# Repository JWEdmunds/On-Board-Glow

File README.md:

#Micro On-board glow driver project.

Compact 4.8V - 8.4V PWM operated glow driver for RC aircraft

The PCB was designed to be as small as possible without turning it into a fuse. 10x20mm with 0201 components and WLCSP all over the shop.

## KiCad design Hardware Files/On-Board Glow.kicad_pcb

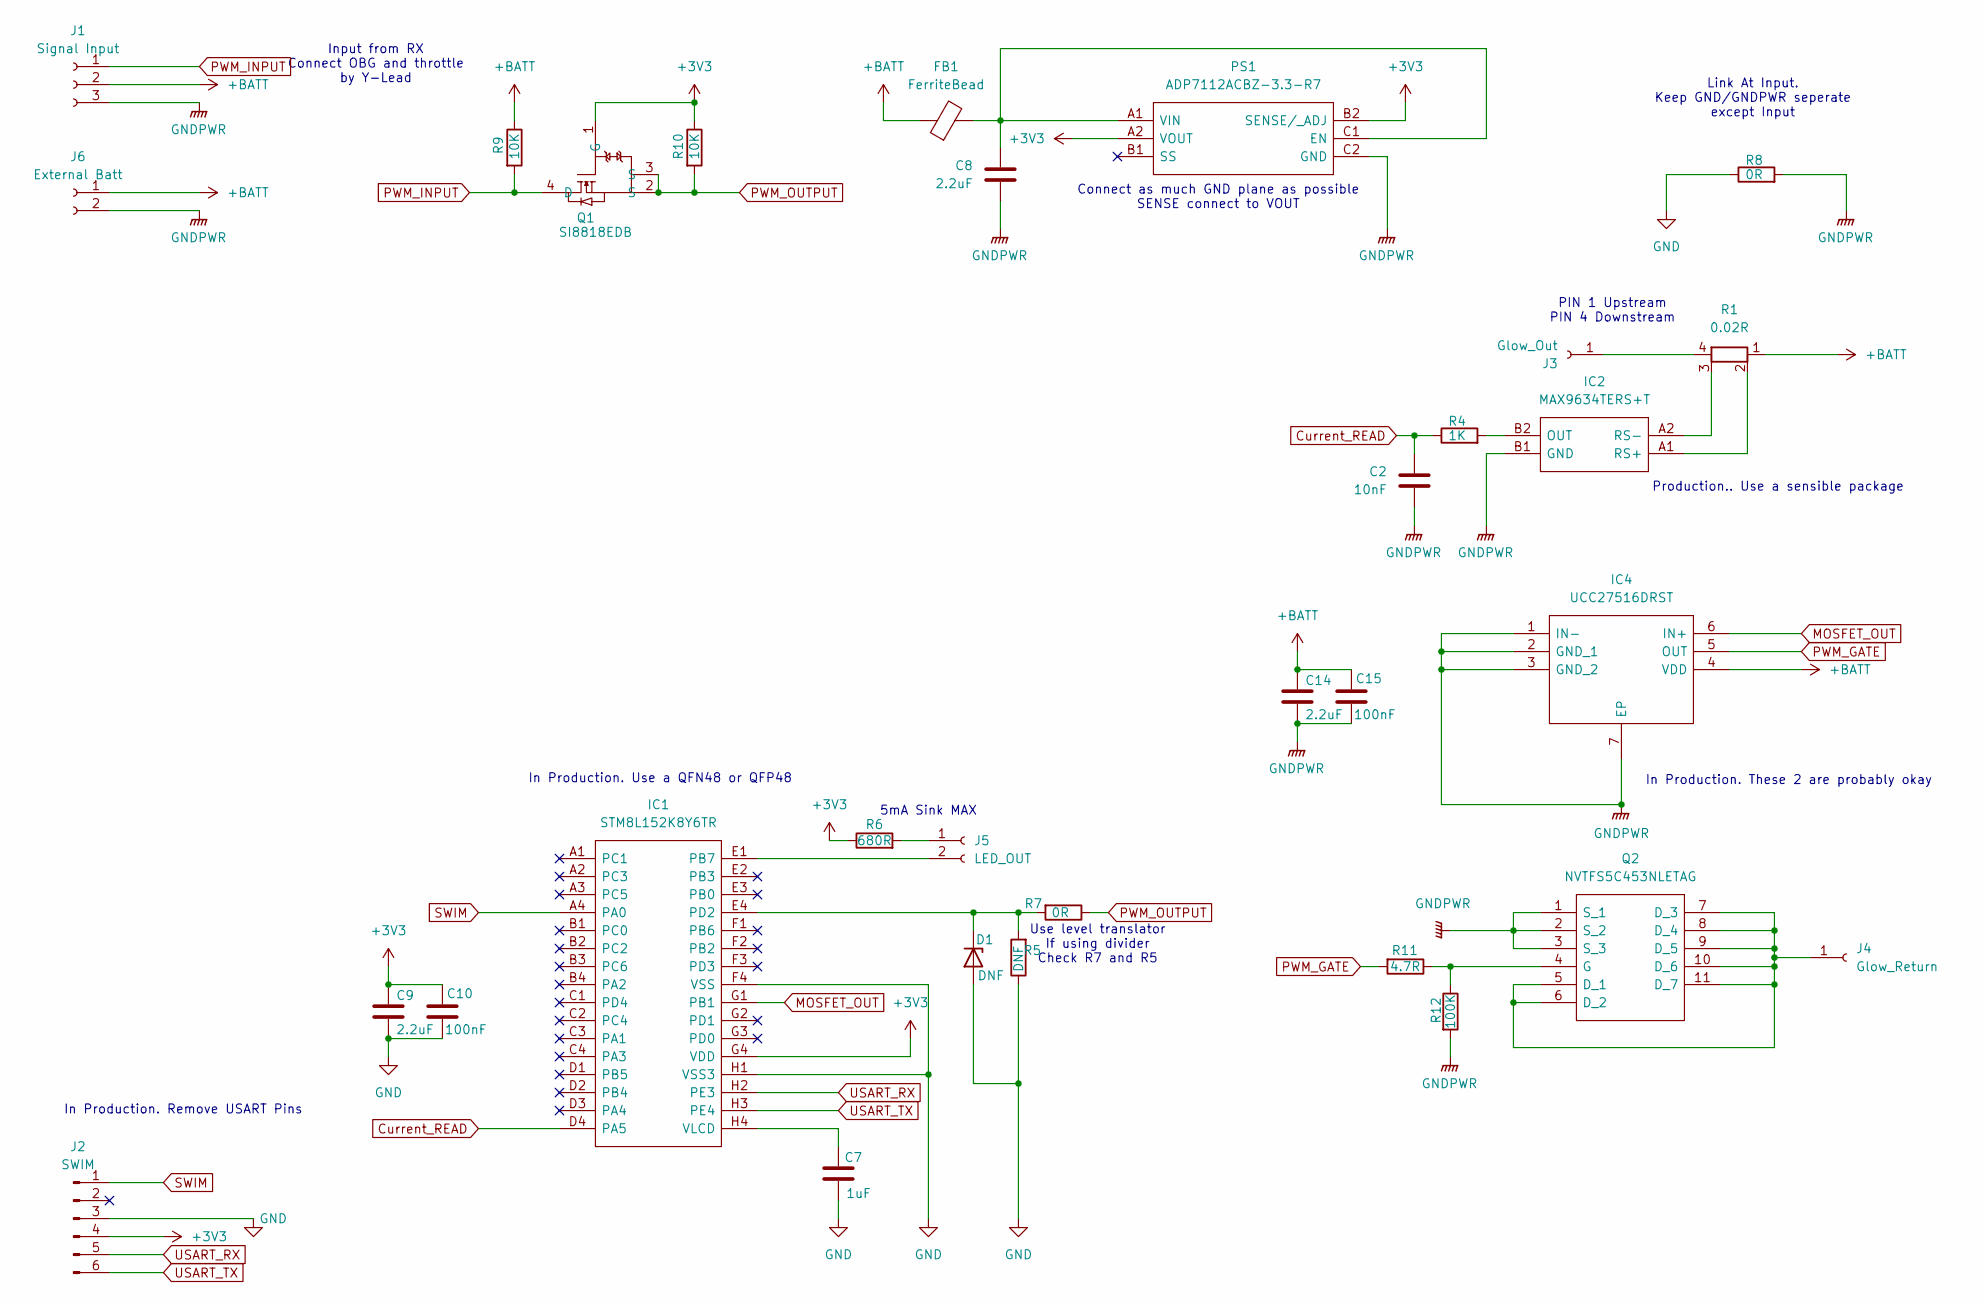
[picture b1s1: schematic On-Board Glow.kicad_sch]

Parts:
C2: 10nF; C_0201_0603Metric
C7: 1uF; C_0201_0603Metric
C8, C9, C14: 2.2uF; C_0201_0603Metric
C10, C15: 100nF; C_0201_0603Metric
D1: DNF; D_0201_0603Metric
FB1: FerriteBead; L_0402_1005Metric
IC1: STM8L152K8Y6TR; BGA32C40P4X8_191X333X58; Manufacturer_Part_Number STM8L152K8Y6TR; Mouser Part Number 511-STM8L152K8Y6TR
IC2: MAX9634TERS+T; BGA4C50P2X2_100X100X69; Manufacturer_Part_Number MAX9634TERS+T; Mouser Part Number 700-MAX9634TERST
IC4: UCC27516DRST; SON95P300X300X80-7N-D; Manufacturer_Part_Number UCC27516DRST; Mouser Part Number 595-UCC27516DRST
J1: Signal Input; Servo_Conn 1x3
J2: SWIM; uHeader
J3: Glow_Out; TestPoint_Pad_2.0x2.0mm
J4: Glow_Return; TestPoint_Pad_2.0x2.0mm
J5: LED_OUT; LED_Conn 1x2
J6: External Batt; Servo_Conn 1x2
PS1: ADP7112ACBZ-3.3-R7; BGA6C40P2X3_95X116X56; Manufacturer_Part_Number ADP7112ACBZ-3.3-R7; Mouser Part Number 584-ADP7112ACBZ3.3R7
Q1: SI8818EDB; Si8818EDB
Q2: NVTFS5C453NLETAG; NTTFS015N04CTAG; Manufacturer_Part_Number NVTFS5C453NLETAG
R1: 0.02R; R_Shunt_Vishay_WSK2512_6332Metric_T1.19mm
R4: 1K; R_0201_0603Metric
R5: DNF; R_0201_0603Metric
R6: 680R; R_0201_0603Metric
R7, R8: 0R; R_0201_0603Metric
R9, R10: 10K; R_0201_0603Metric
R11: 4.7R; R_0201_0603Metric
R12: 100K; R_0201_0603Metric

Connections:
+3V3: C9.1, C10.1, IC1.G4 (VDD), J2.4, PS1.A2 (VOUT), PS1.B2 (SENSE/_ADJ), Q1.1 (G), R6.1, R10.1
+BATT: C14.1, C15.1, FB1.1, IC4.4 (VDD), J1.2, J6.1, R1.1, R9.1
Current_READ: C2.1, IC1.D4 (PA5), R4.1
GND: C7.1, C9.2, C10.2, D1.2 (A), IC1.F4 (VSS), IC1.H1 (VSS3), J2.3, R5.1, R8.1
GNDPWR: C2.2, C8.2, C14.2, C15.2, IC2.B1 (GND), IC4.1 (IN-), IC4.2 (GND_1), IC4.3 (GND_2), IC4.7 (EP), J1.3, J6.2, PS1.C2 (GND), Q2.1 (S_1), Q2.2 (S_2), Q2.3 (S_3), R8.2, R12.2
MOSFET_OUT: IC1.G1 (PB1), IC4.6 (IN+)
unnamed: D1.1 (K), IC1.E4 (PD2), R5.2, R7.2
unnamed: IC1.E1 (PB7), J5.2
unnamed: C7.2, IC1.H4 (VLCD)
unnamed: IC2.B2 (OUT), R4.2
unnamed: IC2.A1 (RS+), R1.2
unnamed: IC2.A2 (RS-), R1.3
unnamed: J3.1 (Pin_1_1), R1.4
unnamed: J4.1 (Pin_1_1), Q2.5 (D_1), Q2.6 (D_2), Q2.7 (D_3), Q2.8 (D_4), Q2.9 (D_5), Q2.10 (D_6), Q2.11 (D_7)
unnamed: J5.1, R6.2
unnamed: C8.1, FB1.2, PS1.A1 (VIN), PS1.C1 (EN)
unnamed: Q2.4 (G), R11.1, R12.1
PWM_GATE: IC4.5 (OUT), R11.2
PWM_INPUT: J1.1, Q1.4 (D), R9.2
PWM_OUTPUT: Q1.2 (S), Q1.3 (S), R7.1, R10.2
SWIM: IC1.A4 (PA0), J2.1
USART_RX: IC1.H2 (PE3), J2.5
USART_TX: IC1.H3 (PE4), J2.6

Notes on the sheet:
PIN 1 Upstream PIN 4 Downstream
Link At Input. Keep GND/GNDPWR seperate except Input
5mA Sink MAX
In Production. These 2 are probably okay
In Production. Use a QFN48 or QFP48
In Production. Remove USART Pins
Use level translator If using divider Check R7 and R5
Production.. Use a sensible package
Connect as much GND plane as possible SENSE connect to VOUT
Input from RX Connect OBG and throttle by Y-Lead

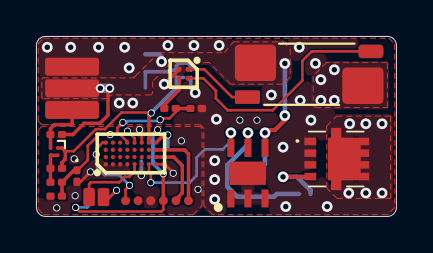
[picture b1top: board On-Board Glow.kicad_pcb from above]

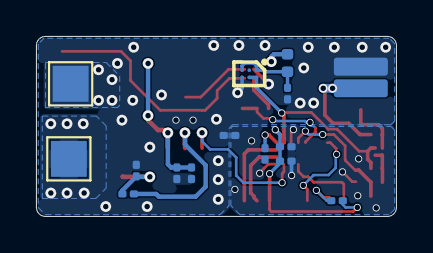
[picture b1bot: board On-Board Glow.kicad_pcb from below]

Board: 2 copper layers, 20.0 x 10.0 mm, 31 parts (15 on the bottom side), 23 nets.
